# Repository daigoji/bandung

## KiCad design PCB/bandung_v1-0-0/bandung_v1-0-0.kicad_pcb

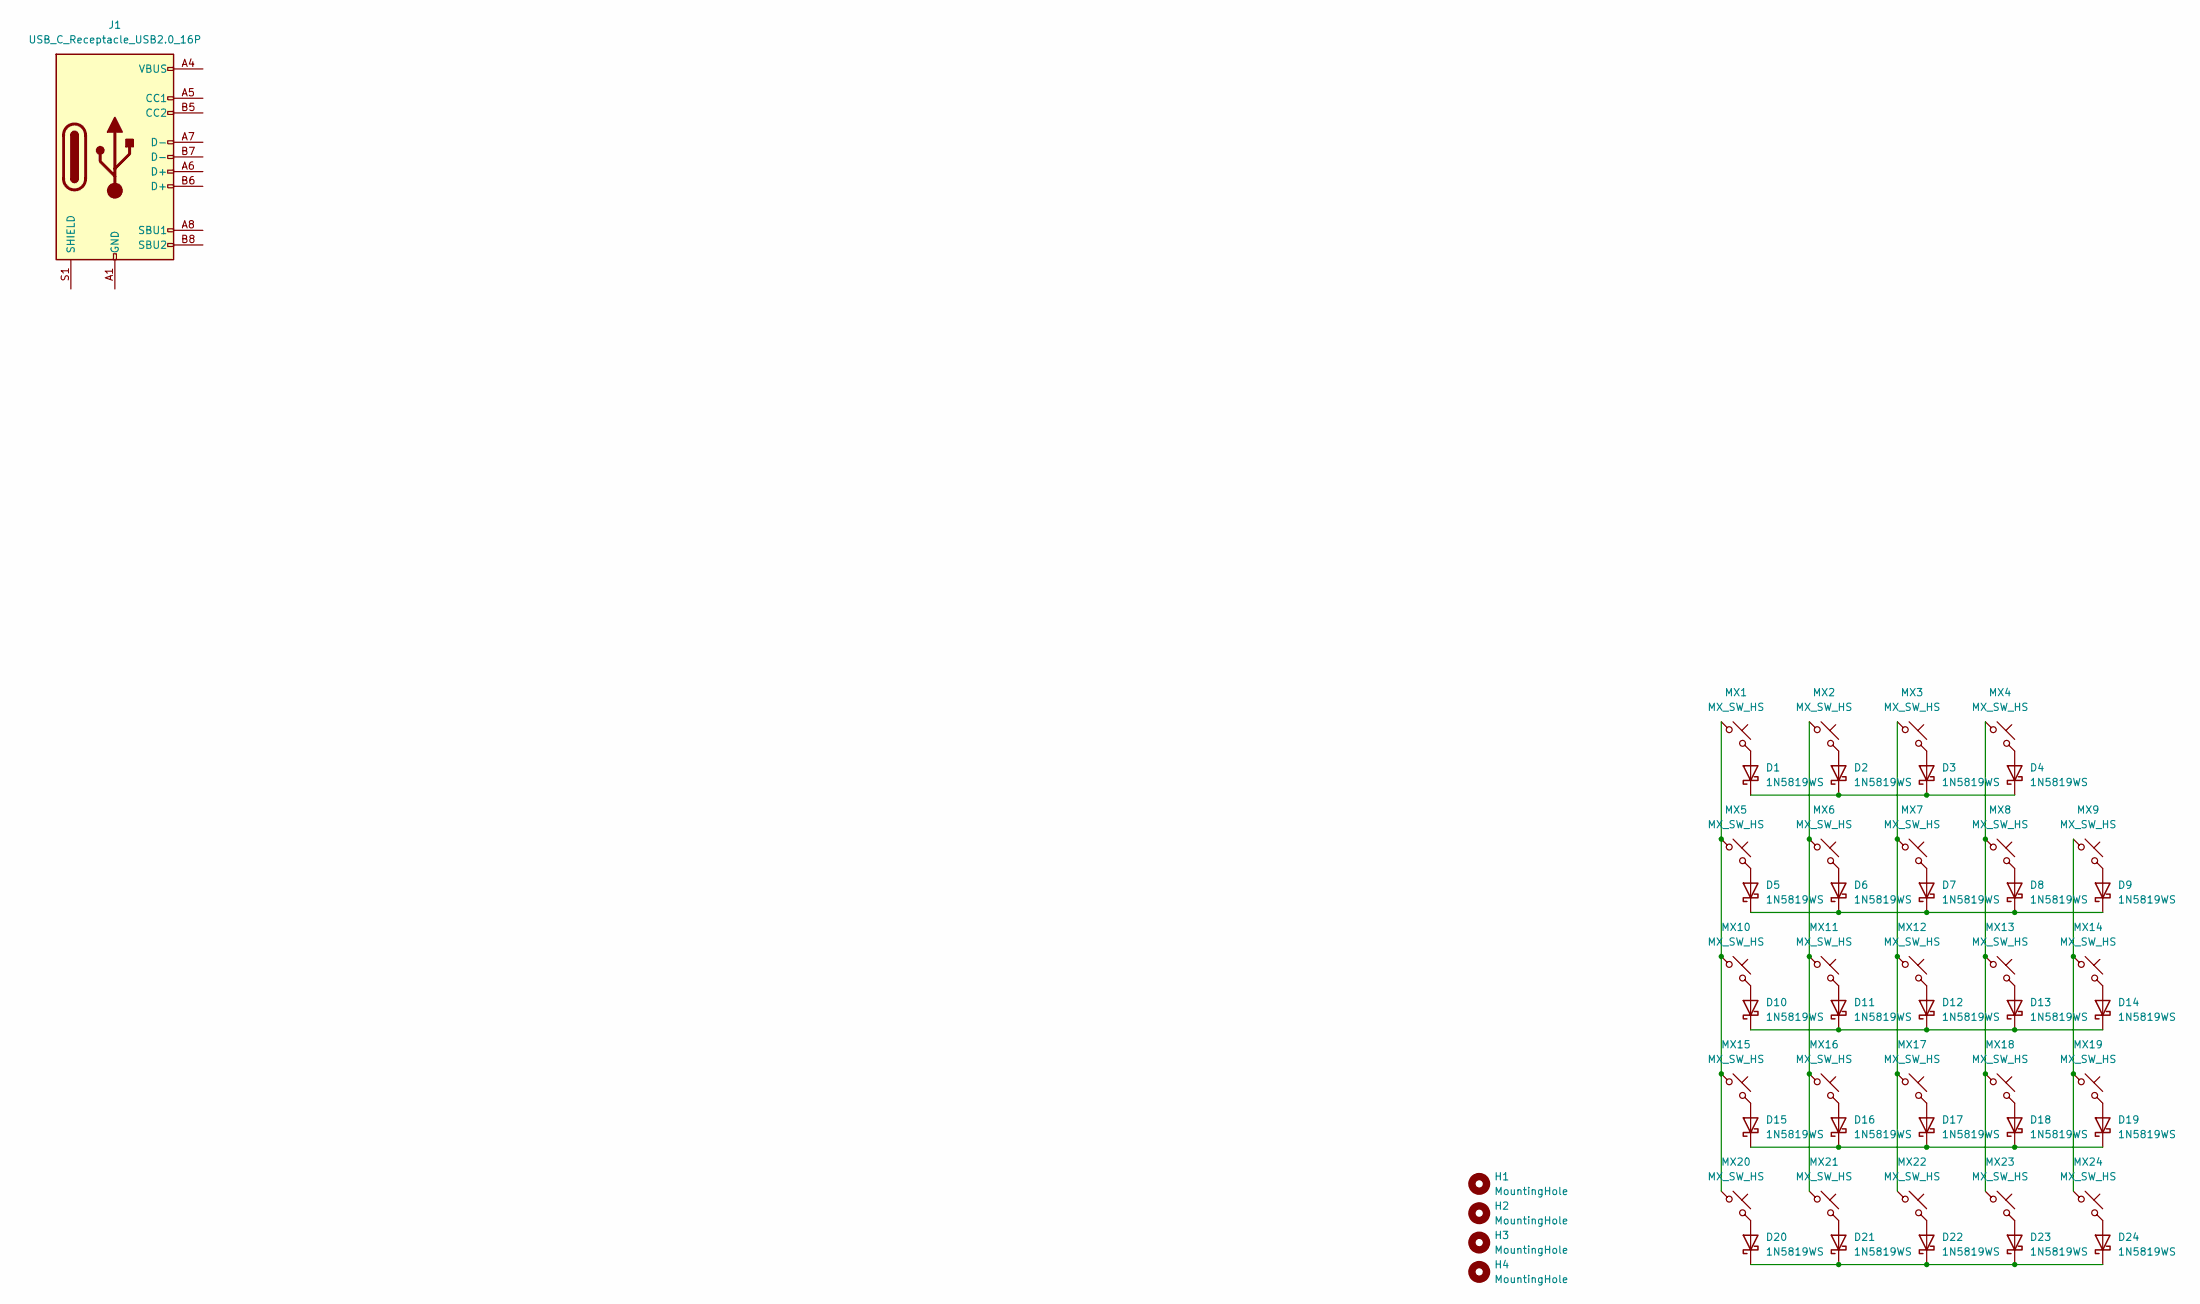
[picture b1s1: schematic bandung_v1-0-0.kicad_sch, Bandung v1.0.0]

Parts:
D1, D2, D3, D4, D5, D6, D7, D8, D9, D10, D11, D12, D13, D14, D15, D16, D17, D18, D19, D20, D21, D22, D23, D24: 1N5819WS; D_SOD-323
H1, H2, H3, H4: MountingHole; MountingHole_3.2mm_M3
J1: USB_C_Receptacle_USB2.0_16P; USB_C_Receptacle_GCT_USB4085
MX1, MX2, MX3, MX4, MX5, MX6, MX7, MX8, MX9, MX10, MX11, MX12, MX13, MX14, MX15, MX16, MX17, MX18, MX19, MX20, MX21, MX22, MX23, MX24: MX_SW_HS; SW_MX_HS_CPG151101S11_1u

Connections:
unnamed: D1.2 (A), MX1.2
unnamed: D1.1 (K), D2.1 (K), D3.1 (K), D4.1 (K)
unnamed: D2.2 (A), MX2.2
unnamed: D3.2 (A), MX3.2
unnamed: D4.2 (A), MX4.2
unnamed: D5.2 (A), MX5.2
unnamed: D5.1 (K), D6.1 (K), D7.1 (K), D8.1 (K), D9.1 (K)
unnamed: D6.2 (A), MX6.2
unnamed: D7.2 (A), MX7.2
unnamed: D8.2 (A), MX8.2
unnamed: D9.2 (A), MX9.2
unnamed: D10.2 (A), MX10.2
unnamed: D10.1 (K), D11.1 (K), D12.1 (K), D13.1 (K), D14.1 (K)
unnamed: D11.2 (A), MX11.2
unnamed: D12.2 (A), MX12.2
unnamed: D13.2 (A), MX13.2
unnamed: D14.2 (A), MX14.2
unnamed: D15.2 (A), MX15.2
unnamed: D15.1 (K), D16.1 (K), D17.1 (K), D18.1 (K), D19.1 (K)
unnamed: D16.2 (A), MX16.2
unnamed: D17.2 (A), MX17.2
unnamed: D18.2 (A), MX18.2
unnamed: D19.2 (A), MX19.2
unnamed: D20.2 (A), MX20.2
unnamed: D20.1 (K), D21.1 (K), D22.1 (K), D23.1 (K), D24.1 (K)
unnamed: D21.2 (A), MX21.2
unnamed: D22.2 (A), MX22.2
unnamed: D23.2 (A), MX23.2
unnamed: D24.2 (A), MX24.2
unnamed: J1.A1 (GND), J1.A12 (GND), J1.B1 (GND), J1.B12 (GND)
unnamed: J1.A4 (VBUS), J1.A9 (VBUS), J1.B4 (VBUS), J1.B9 (VBUS)
unnamed: MX1.1, MX5.1, MX10.1, MX15.1, MX20.1
unnamed: MX2.1, MX6.1, MX11.1, MX16.1, MX21.1
unnamed: MX3.1, MX7.1, MX12.1, MX17.1, MX22.1
unnamed: MX4.1, MX8.1, MX13.1, MX18.1, MX23.1
unnamed: MX9.1, MX14.1, MX19.1, MX24.1

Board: 2 copper layers, 53 parts (49 on the bottom side), 36 nets, no tracks yet.

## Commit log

2024-06-17 Keyboard Layout Editor
